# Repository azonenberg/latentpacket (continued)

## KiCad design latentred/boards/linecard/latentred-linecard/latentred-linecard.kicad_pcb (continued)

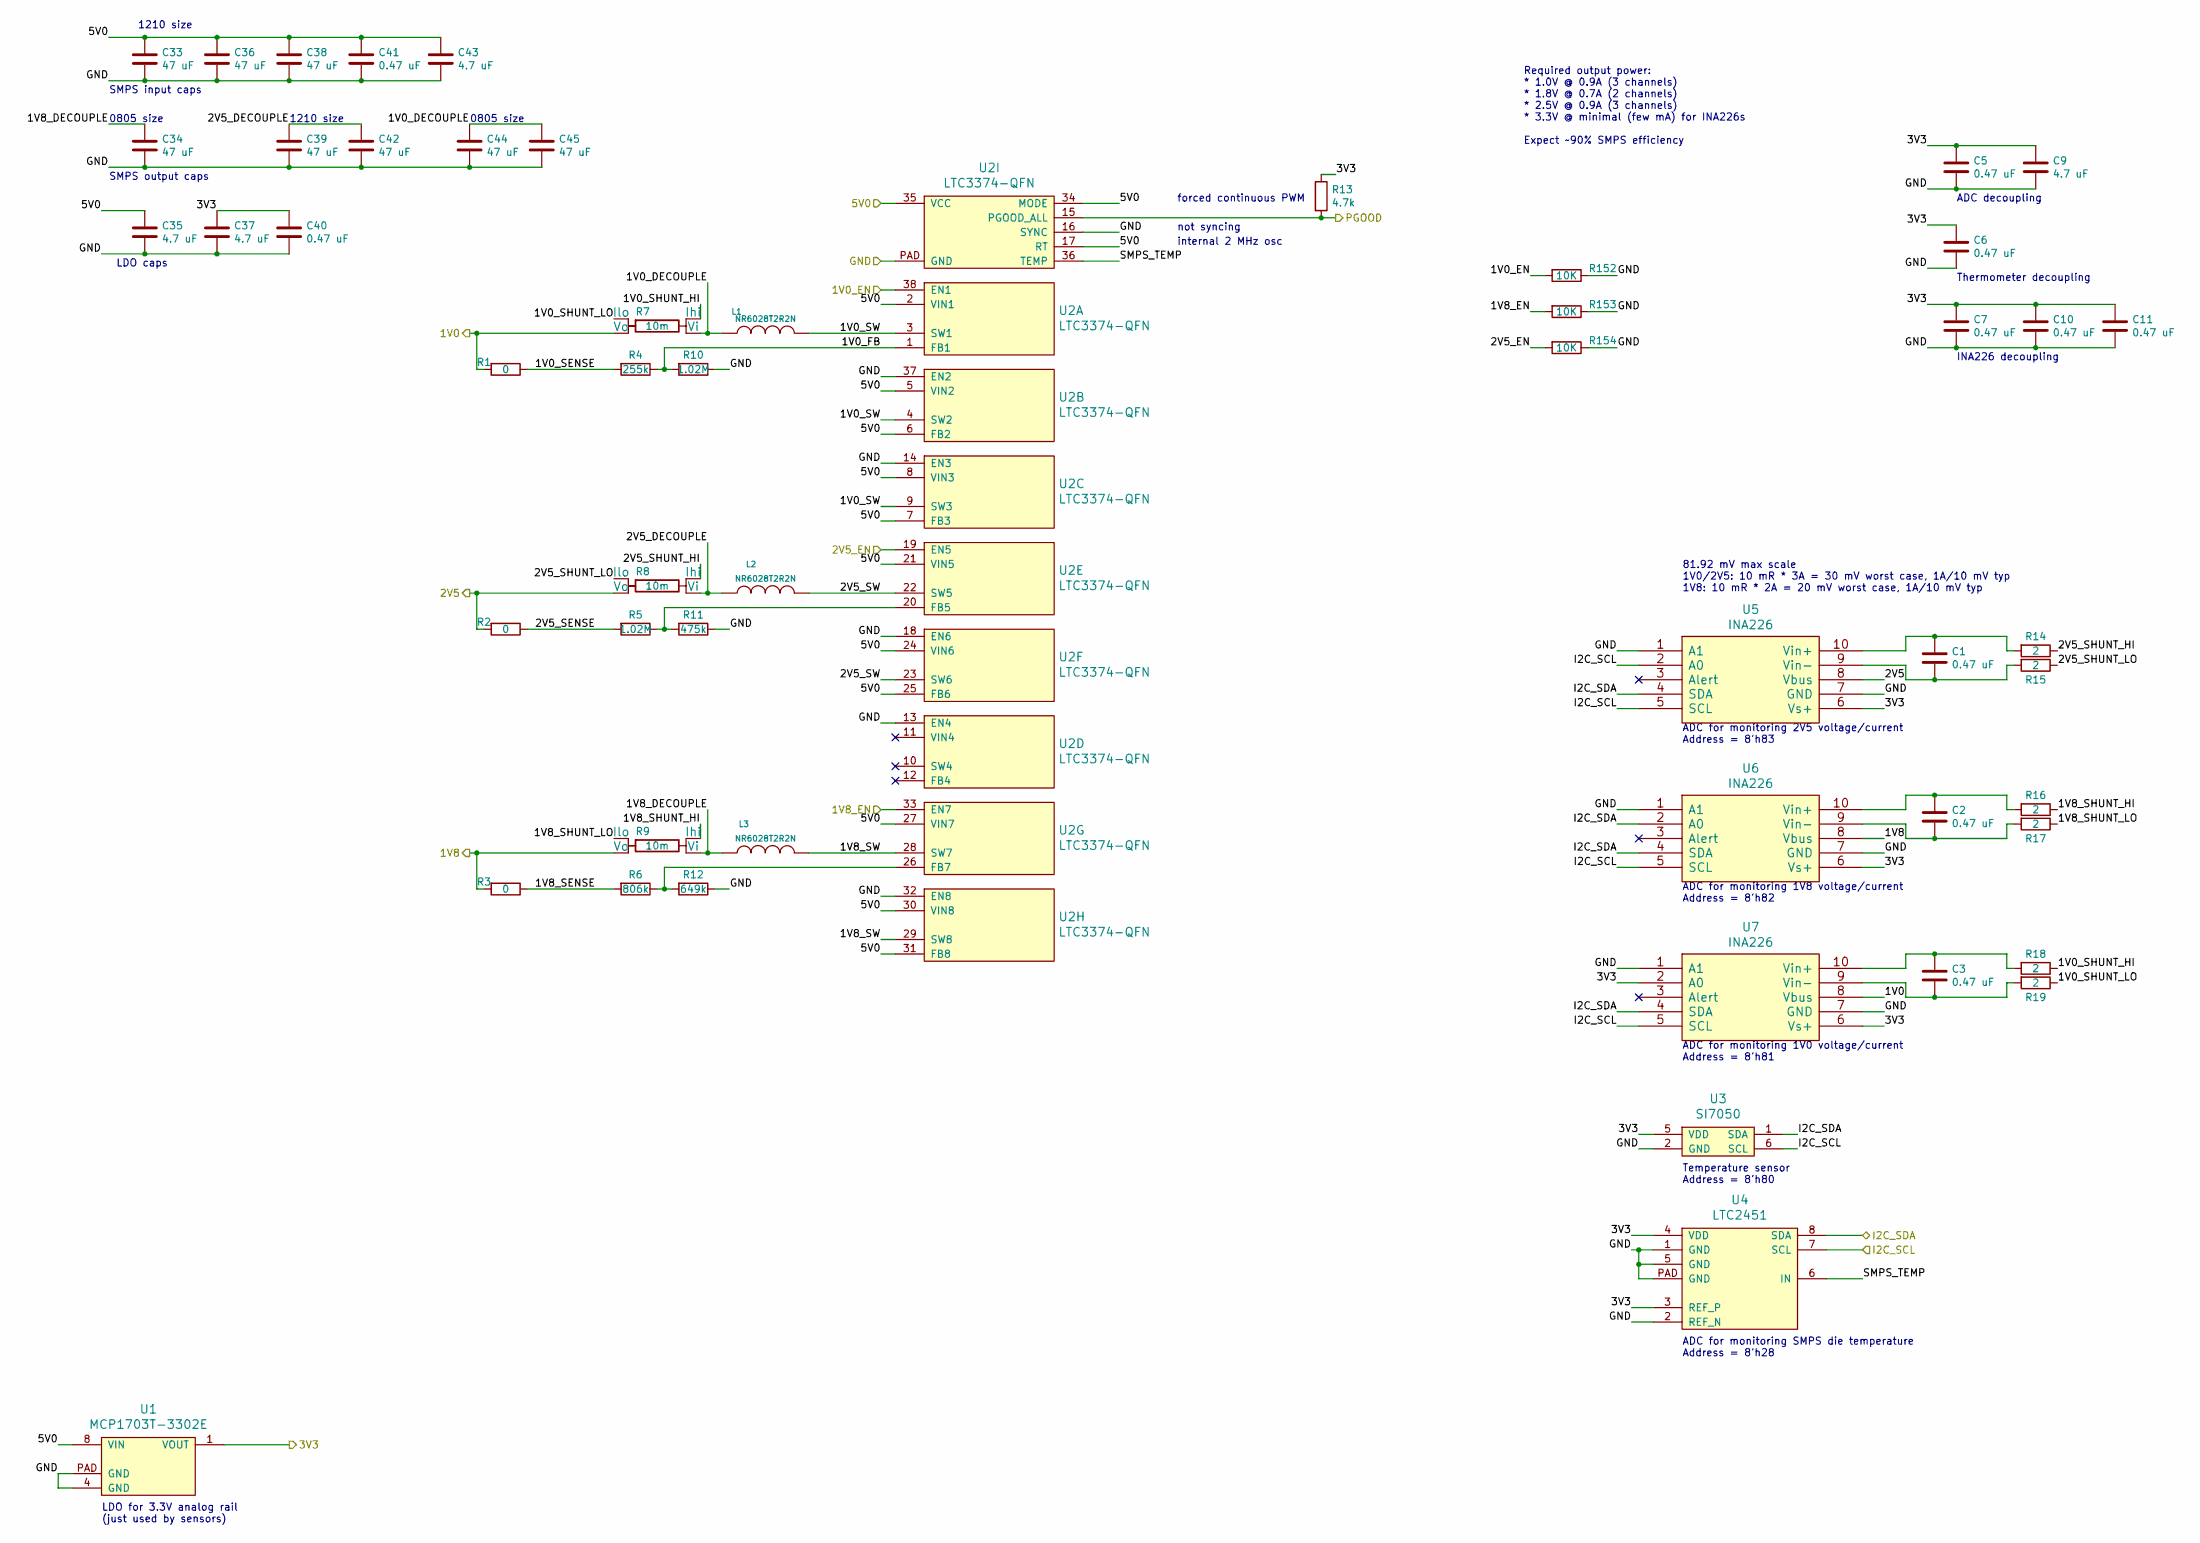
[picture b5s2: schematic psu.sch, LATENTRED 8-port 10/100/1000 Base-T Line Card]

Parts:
C1, C2, C3, C5, C6, C7, C10, C11, C40, C41: 0.47 uF; EIA_0402_CAP_NOSILK
C9, C35, C37, C43: 4.7 uF; EIA_0603_CAP_NOSILK
C33, C36, C38, C39, C42: 47 uF; EIA_1210_CAP_NOSILK
C34, C44, C45: 47 uF; EIA_0805_CAP_NOSILK
L1, L2, L3: NR6028T2R2N; INDUCTOR_YUDEN_NR6028
R1, R2, R3: 0; EIA_0402_RES_NOSILK
R4: 255k; EIA_0402_RES_NOSILK
R5, R10: 1.02M; EIA_0402_RES_NOSILK
R6: 806k; EIA_0402_RES_NOSILK
R7, R8, R9: 10m; OHMITE_LVK12
R11: 475k; EIA_0402_RES_NOSILK
R12: 649k; EIA_0402_RES_NOSILK
R13: 4.7k; EIA_0402_RES_NOSILK
R14, R15, R16, R17, R18, R19: 2; EIA_0402_RES_NOSILK
R152, R153, R154: 10K; EIA_0402_RES_NOSILK
U1: MCP1703T-3302E; DFN_8_0.5MM_3x3MM
U2: LTC3374-QFN; QFN_38_0.5MM_5x7MM
U3: SI7050; DFN_6_1MM_3x3MM
U4: LTC2451; DFN_8_0.5MM_2x3MM
U5, U6, U7: INA226; SOP_10_0.5MM_3MM

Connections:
/1V0_EN: R152.2, U2.38 (EN1); also elsewhere on the board
/1V8_EN: R153.2, U2.33 (EN7); also elsewhere on the board
/2V5_EN: R154.2, U2.19 (EN5); also elsewhere on the board
/3V3: C5.1, C6.1, C7.1, C9.1, C10.1, C11.1, C37.1, C40.1, R13.1, U1.1 (VOUT), U3.5 (VDD), U4.3 (REF_P), U4.4 (VDD), U5.6 (Vs+), U6.6 (Vs+), U7.2 (A0), U7.6 (Vs+); also elsewhere on the board
/5V0: C33.1, C35.1, C36.1, C38.1, C41.1, C43.1, U1.8 (VIN), U2.2 (VIN1), U2.5 (VIN2), U2.6 (FB2), U2.7 (FB3), U2.8 (VIN3), U2.17 (RT), U2.21 (VIN5), U2.24 (VIN6), U2.25 (FB6), U2.27 (VIN7), U2.30 (VIN8), U2.31 (FB8), U2.34 (MODE), U2.35 (VCC); also elsewhere on the board
/GND: C5.2, C6.2, C7.2, C9.2, C10.2, C11.2, C33.2, C34.2, C35.2, C36.2, C37.2, C38.2, C39.2, C40.2, C41.2, C42.2, C43.2, C44.2, C45.2, R10.1, R11.1, R12.1, R152.1, R153.1, R154.1, U1.4 (GND), U1.PAD (GND), U2.13 (EN4), U2.14 (EN3), U2.16 (SYNC), U2.18 (EN6), U2.32 (EN8), U2.37 (EN2), U2.PAD (GND), U3.2 (GND), U4.1 (GND), U4.2 (REF_N), U4.5 (GND), U4.PAD (GND), U5.1 (A1), U5.7 (GND), U6.1 (A1), U6.7 (GND), U7.1 (A1), U7.7 (GND); also elsewhere on the board
/I2C_SCL: U3.6 (SCL), U4.7 (SCL), U5.2 (A0), U5.5 (SCL), U6.5 (SCL), U7.5 (SCL); also elsewhere on the board
/I2C_SDA: U3.1 (SDA), U4.8 (SDA), U5.4 (SDA), U6.2 (A0), U6.4 (SDA), U7.4 (SDA); also elsewhere on the board
/PHYs/1V0: R1.2, R7.2 (Vo), U7.8 (Vbus); also elsewhere on the board
/PHYs/1V8: R3.2, R9.2 (Vo), U6.8 (Vbus); also elsewhere on the board
/PHYs/2V5: R2.2, R8.2 (Vo), U5.8 (Vbus); also elsewhere on the board
/PSU_PGOOD: R13.2, U2.15 (PGOOD_ALL); also elsewhere on the board
/Power Supply/1V0_DECOUPLE: C44.1, C45.1, L1.1, R7.4 (Vi)
/Power Supply/1V0_FB: R4.1, R10.2, U2.1 (FB1)
/Power Supply/1V0_SENSE: R1.1, R4.2
/Power Supply/1V0_SHUNT_HI: R7.3 (Ihi), R18.1
/Power Supply/1V0_SHUNT_LO: R7.1 (Ilo), R19.1
/Power Supply/1V0_SW: L1.2, U2.3 (SW1), U2.4 (SW2), U2.9 (SW3)
/Power Supply/1V8_DECOUPLE: C34.1, L3.1, R9.4 (Vi)
/Power Supply/1V8_SENSE: R3.1, R6.2
/Power Supply/1V8_SHUNT_HI: R9.3 (Ihi), R16.1
/Power Supply/1V8_SHUNT_LO: R9.1 (Ilo), R17.1
/Power Supply/1V8_SW: L3.2, U2.28 (SW7), U2.29 (SW8)
/Power Supply/2V5_DECOUPLE: C39.1, C42.1, L2.1, R8.4 (Vi)
/Power Supply/2V5_SENSE: R2.1, R5.2
/Power Supply/2V5_SHUNT_HI: R8.3 (Ihi), R14.1
/Power Supply/2V5_SHUNT_LO: R8.1 (Ilo), R15.1
/Power Supply/2V5_SW: L2.2, U2.22 (SW5), U2.23 (SW6)
/Power Supply/SMPS_TEMP: U2.36 (TEMP), U4.6 (IN)
unnamed: C1.1, R14.2, U5.10 (Vin+)
unnamed: C1.2, R15.2, U5.9 (Vin-)
unnamed: C2.1, R16.2, U6.10 (Vin+)
unnamed: C2.2, R17.2, U6.9 (Vin-)
unnamed: C3.1, R18.2, U7.10 (Vin+)
unnamed: C3.2, R19.2, U7.9 (Vin-)
unnamed: R5.1, R11.2, U2.20 (FB5)
unnamed: R6.1, R12.2, U2.26 (FB7)

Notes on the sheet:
Required output power: * 1.0V @ 0.9A (3 channels) * 1.8V @ 0.7A (2 channels) * 2.5V @ 0.9A (3 channels) * 3.3V @ minimal (few mA) for INA226s Expect ~~90% SMPS efficiency
forced continuous PWM
internal 2 MHz osc
not syncing
ADC for monitoring SMPS die temperature Address = 8'h28
LDO for 3.3V analog rail (just used by sensors)
ADC decoupling
Temperature sensor Address = 8'h80
Thermometer decoupling
ADC for monitoring 1V0 voltage/current Address = 8'h81
ADC for monitoring 1V8 voltage/current Address = 8'h82
ADC for monitoring 2V5 voltage/current Address = 8'h83
INA226 decoupling
81.92 mV max scale 1V0/2V5: 10 mR * 3A = 30 mV worst case, 1A/10 mV typ 1V8: 10 mR * 2A = 20 mV worst case, 1A/10 mV typ
SMPS input caps
SMPS output caps
LDO caps
1210 size
0805 size
